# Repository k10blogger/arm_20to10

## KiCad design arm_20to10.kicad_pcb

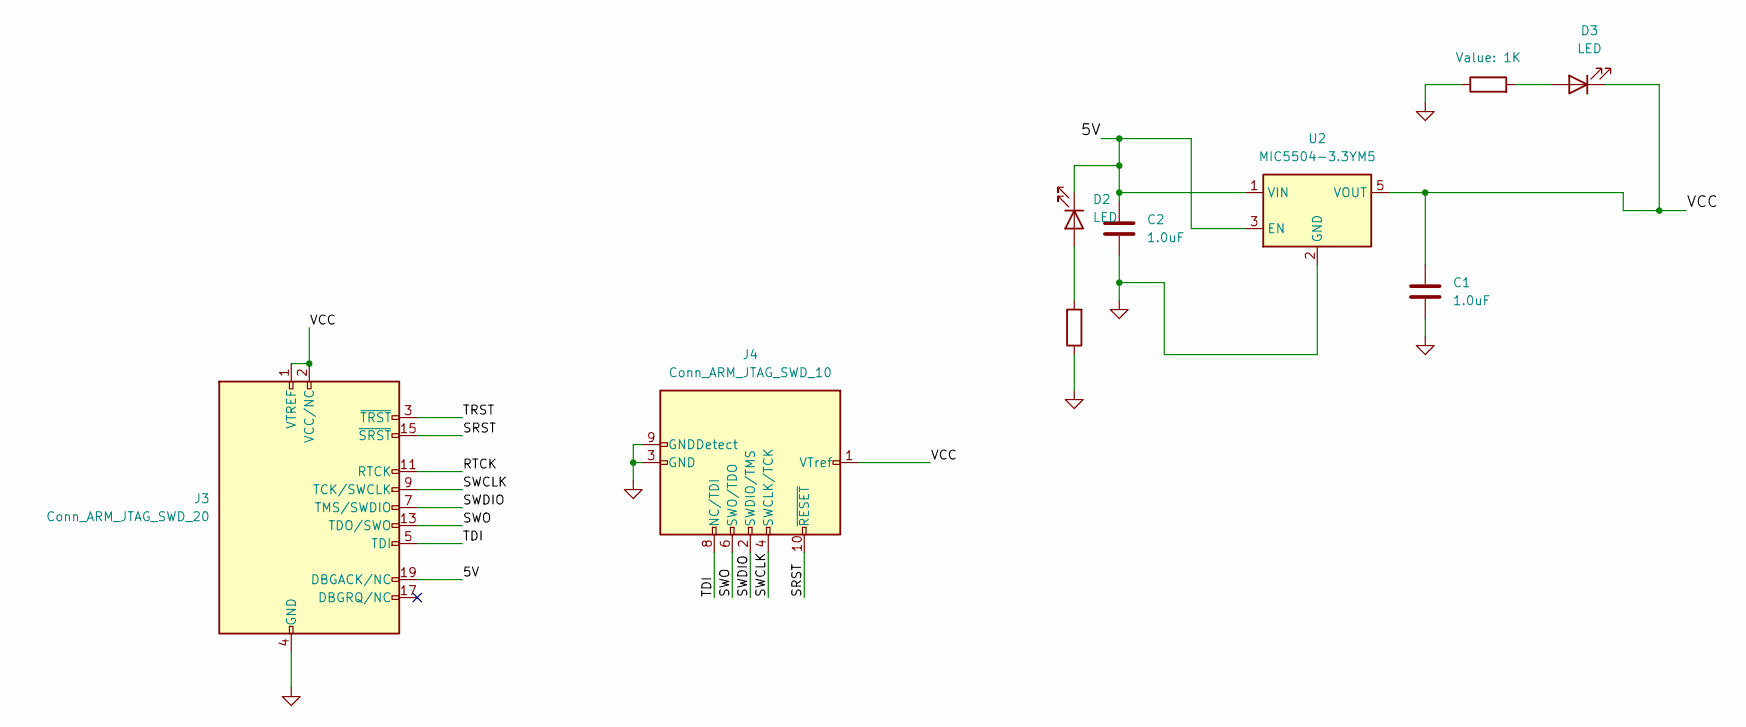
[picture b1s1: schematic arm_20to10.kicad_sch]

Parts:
C1, C2: 1.0uF; C_0603_1608Metric_Pad1.08x0.95mm_HandSolder
D2, D3: LED; LED_0603_1608Metric_Pad1.05x0.95mm_HandSolder
J3: Conn_ARM_JTAG_SWD_20; IDC-Header_2x10_P2.54mm_Latch_Vertical
J4: Conn_ARM_JTAG_SWD_10; PinHeader_2x05_P1.27mm_Horizontal
R2, R3: 1K; R_0603_1608Metric_Pad0.98x0.95mm_HandSolder
U2: MIC5504-3.3YM5; SOT-23-5

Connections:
/5V: C2.1, D2.1 (K), J3.19 (DBGACK/NC), U2.1 (VIN), U2.3 (EN)
/RTCK: J3.11 (RTCK)
/SRST: J3.15 (~SRST), J4.10 (~RESET)
/SWCLK: J3.9 (TCK/SWCLK), J4.4 (SWCLK/TCK)
/SWDIO: J3.7 (TMS/SWDIO), J4.2 (SWDIO/TMS)
/SWO: J3.13 (TDO/SWO), J4.6 (SWO/TDO)
/TDI: J3.5 (TDI), J4.8 (NC/TDI)
/TRST: J3.3 (~TRST)
/VCC: C1.1, D3.1 (K), J3.1 (VTREF), J3.2 (VCC/NC), J4.1 (VTref), U2.5 (VOUT)
GND: C1.2, C2.2, J3.4 (GND), J3.6 (GND), J3.8 (GND), J3.10 (GND), J3.12 (GND), J3.14 (GND), J3.16 (GND), J3.18 (GND), J3.20 (GND), J4.3 (GND), J4.5 (GND), J4.9 (GNDDetect), R2.1, R3.1, U2.2 (GND)
unnamed: D2.2 (A), R2.2
unnamed: D3.2 (A), R3.2

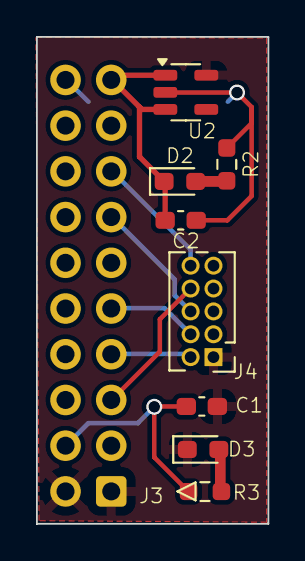
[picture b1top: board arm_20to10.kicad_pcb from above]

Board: 2 copper layers, 12.9 x 27.1 mm, 9 parts (0 on the bottom side), 10 nets.

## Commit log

2025-06-15 Moved to the Kicad 9.0
